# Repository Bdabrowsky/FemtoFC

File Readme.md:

# Hardware files for Open Source flight computer for small diameter rockets
## 17,5x50mm 
## For software, visit [Source Page]([https://github.com/Bdabrowsky/Clockwork_Banana](https://github.com/Bdabrowsky/Clockwork_Banana/tree/Clockwork_Banana_FemtoFC))
## All above hardware is made using funding from [Odkrywcy Diamentów](https://odkrywcydiamentow.com.pl/) grant program

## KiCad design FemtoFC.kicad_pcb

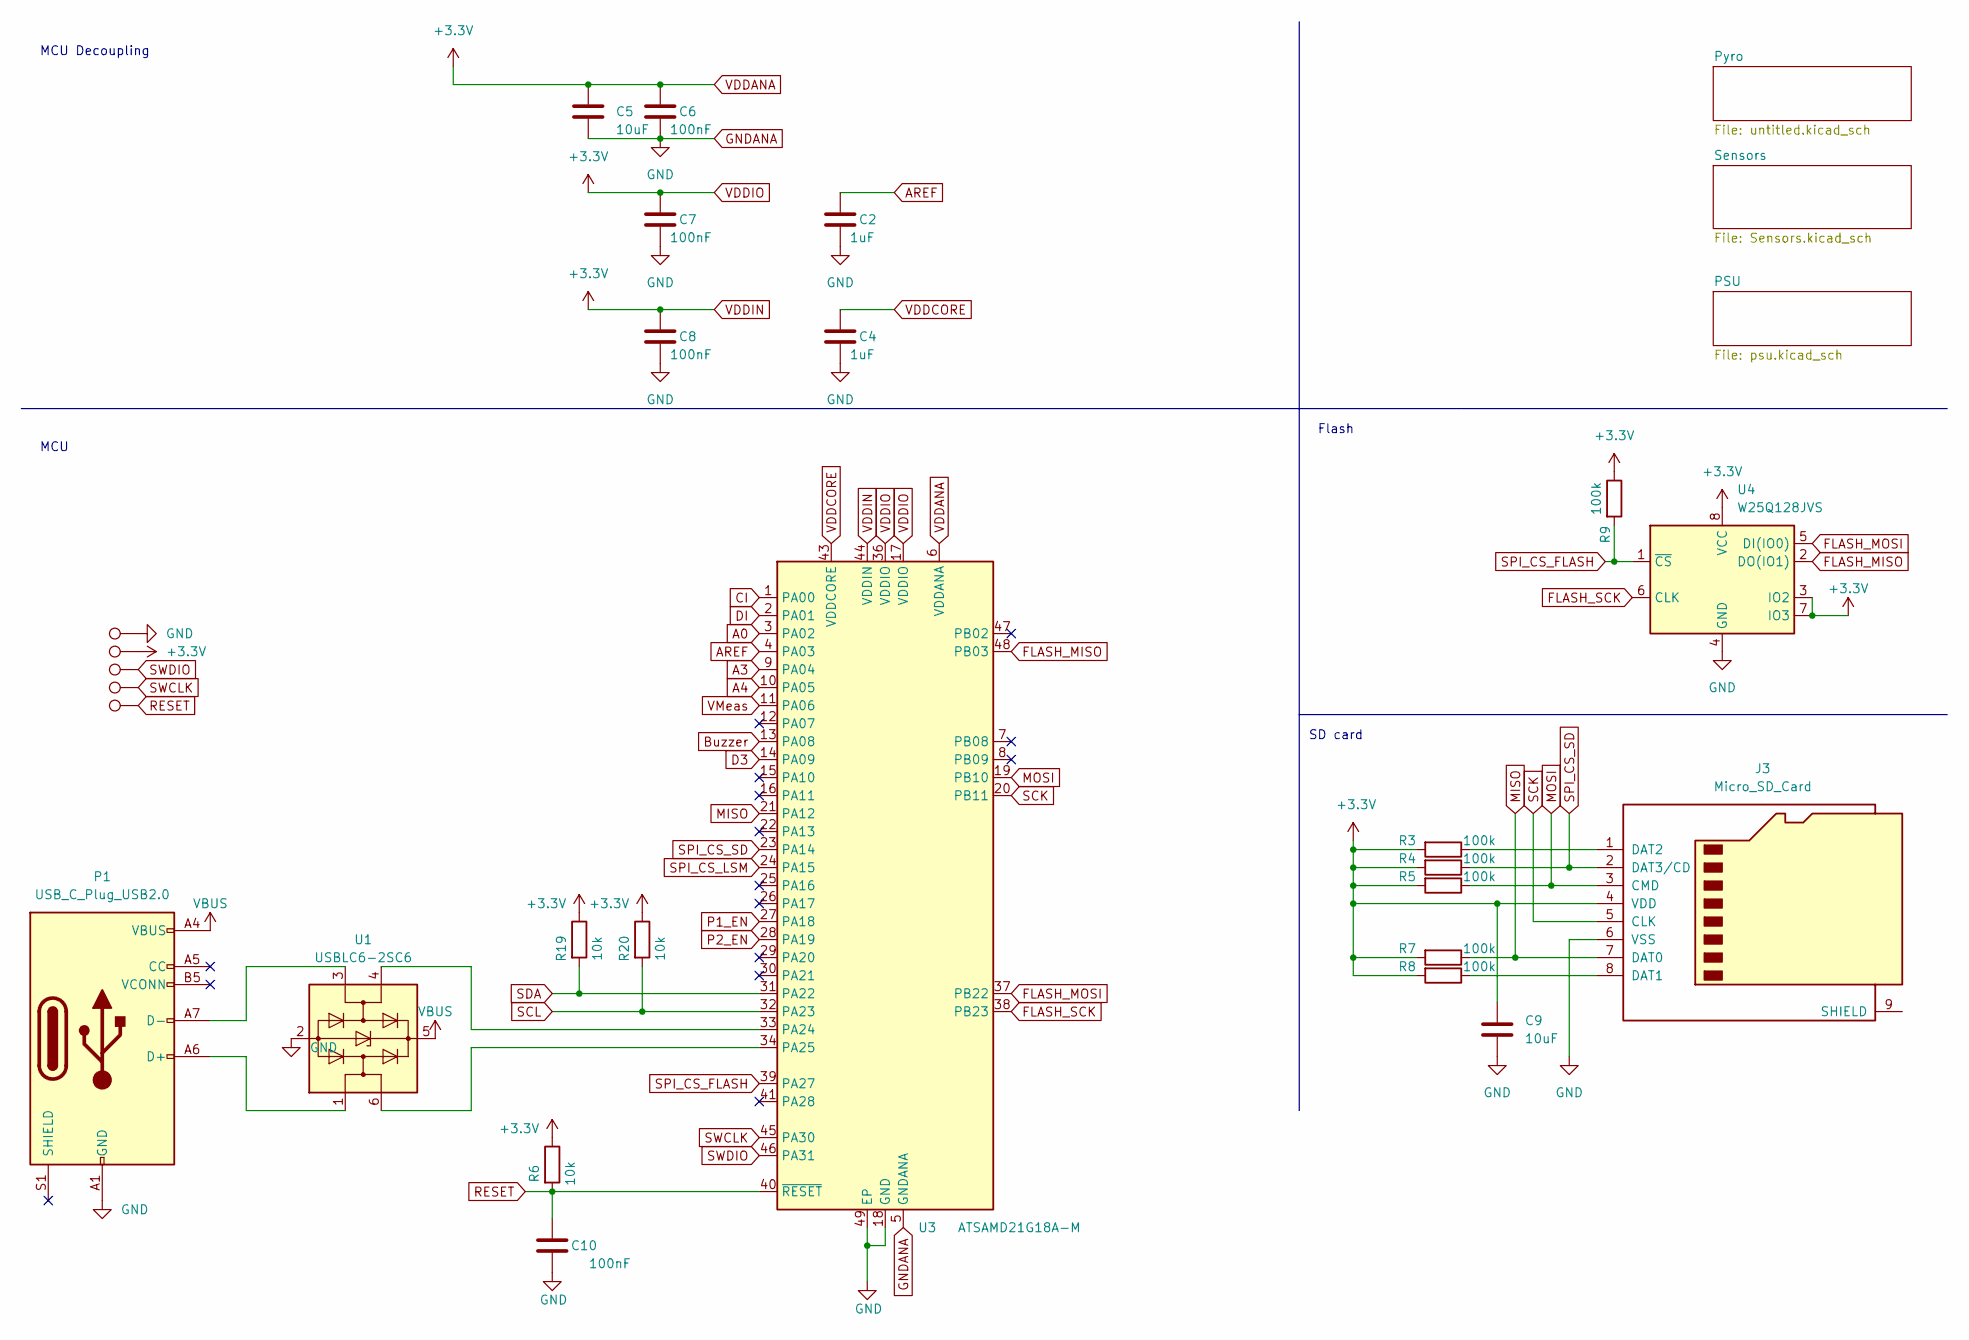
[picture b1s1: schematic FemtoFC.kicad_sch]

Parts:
C2, C4: 1uF; C_0402_1005Metric_Pad0.74x0.62mm_HandSolder
C5, C9: 10uF; C_0402_1005Metric_Pad0.74x0.62mm_HandSolder
C6, C7, C8, C10: 100nF; C_0402_1005Metric_Pad0.74x0.62mm_HandSolder
J3: Micro_SD_Card; microSD_HC_Molex_104031-0811
P1: USB_C_Plug_USB2.0; USB_C_Receptacle_JAE_DX07S016JA1R1500
R3, R4, R5, R7, R8, R9: 100k; R_0402_1005Metric_Pad0.72x0.64mm_HandSolder
R6, R19, R20: 10k; R_0402_1005Metric_Pad0.72x0.64mm_HandSolder
TP1, TP2, TP3, TP4, TP5: TestPoint; TestPoint_Pad_D1.0mm
U1: USBLC6-2SC6; SOT-23-6
U3: ATSAMD21G18A-M; QFN-48-1EP_7x7mm_P0.5mm_EP5.15x5.15mm
U4: W25Q128JVS; WSON-8-1EP_6x5mm_P1.27mm_EP3.4x4.3mm

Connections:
A0: U3.3 (PA02)
A3: U3.9 (PA04)
A4: U3.10 (PA05)
AREF: C2.1, U3.4 (PA03)
Buzzer: U3.13 (PA08); also elsewhere on the board
CI: U3.1 (PA00); also elsewhere on the board
D3: U3.14 (PA09)
DI: U3.2 (PA01); also elsewhere on the board
FLASH_MISO: U3.48 (PB03), U4.2 (DO(IO1))
FLASH_MOSI: U3.37 (PB22), U4.5 (DI(IO0))
FLASH_SCK: U3.38 (PB23), U4.6 (CLK)
GNDANA: C2.2, C4.2, C5.2, C6.2, C7.2, C8.2, C9.2, C10.2, J3.6 (VSS), P1.A1 (GND), P1.A12 (GND), P1.B1 (GND), P1.B12 (GND), TP1.1, U1.2 (GND), U3.5 (GNDANA), U3.18 (GND), U3.35 (GND), U3.42 (GND), U3.49 (EP), U4.4 (GND); also elsewhere on the board
MISO: J3.7 (DAT0), R7.1, U3.21 (PA12); also elsewhere on the board
MOSI: J3.3 (CMD), R5.1, U3.19 (PB10); also elsewhere on the board
unnamed: J3.1 (DAT2), R3.1
unnamed: J3.8 (DAT1), R8.1
unnamed: P1.A6 (D+), U1.1 (I/O1)
unnamed: P1.A7 (D-), U1.3 (I/O2)
unnamed: U1.4 (I/O2), U3.33 (PA24)
unnamed: U1.6 (I/O1), U3.34 (PA25)
P1_EN: U3.27 (PA18); also elsewhere on the board
P2_EN: U3.28 (PA19); also elsewhere on the board
RESET: C10.1, R6.2, TP5.1, U3.40 (~RESET)
SCK: J3.5 (CLK), U3.20 (PB11); also elsewhere on the board
SCL: R20.2, U3.32 (PA23); also elsewhere on the board
SDA: R19.2, U3.31 (PA22); also elsewhere on the board
SPI_CS_FLASH: R9.2, U3.39 (PA27), U4.1 (~CS)
SPI_CS_LSM: U3.24 (PA15); also elsewhere on the board
SPI_CS_SD: J3.2 (DAT3/CD), R4.1, U3.23 (PA14)
SWCLK: TP4.1, U3.45 (PA30)
SWDIO: TP3.1, U3.46 (PA31)
VBUS: P1.A4 (VBUS), P1.A9 (VBUS), P1.B4 (VBUS), P1.B9 (VBUS), U1.5 (VBUS); also elsewhere on the board
VDDANA: C5.1, C6.1, C7.1, C8.1, C9.1, J3.4 (VDD), R3.2, R4.2, R5.2, R6.1, R7.2, R8.2, R9.1, R19.1, R20.1, TP2.1, U3.6 (VDDANA), U3.17 (VDDIO), U3.36 (VDDIO), U3.44 (VDDIN), U4.3 (IO2), U4.7 (IO3), U4.8 (VCC); also elsewhere on the board
VDDCORE: C4.1, U3.43 (VDDCORE)
VMeas: U3.11 (PA06)

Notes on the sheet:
SD card
MCU
Flash
MCU Decoupling

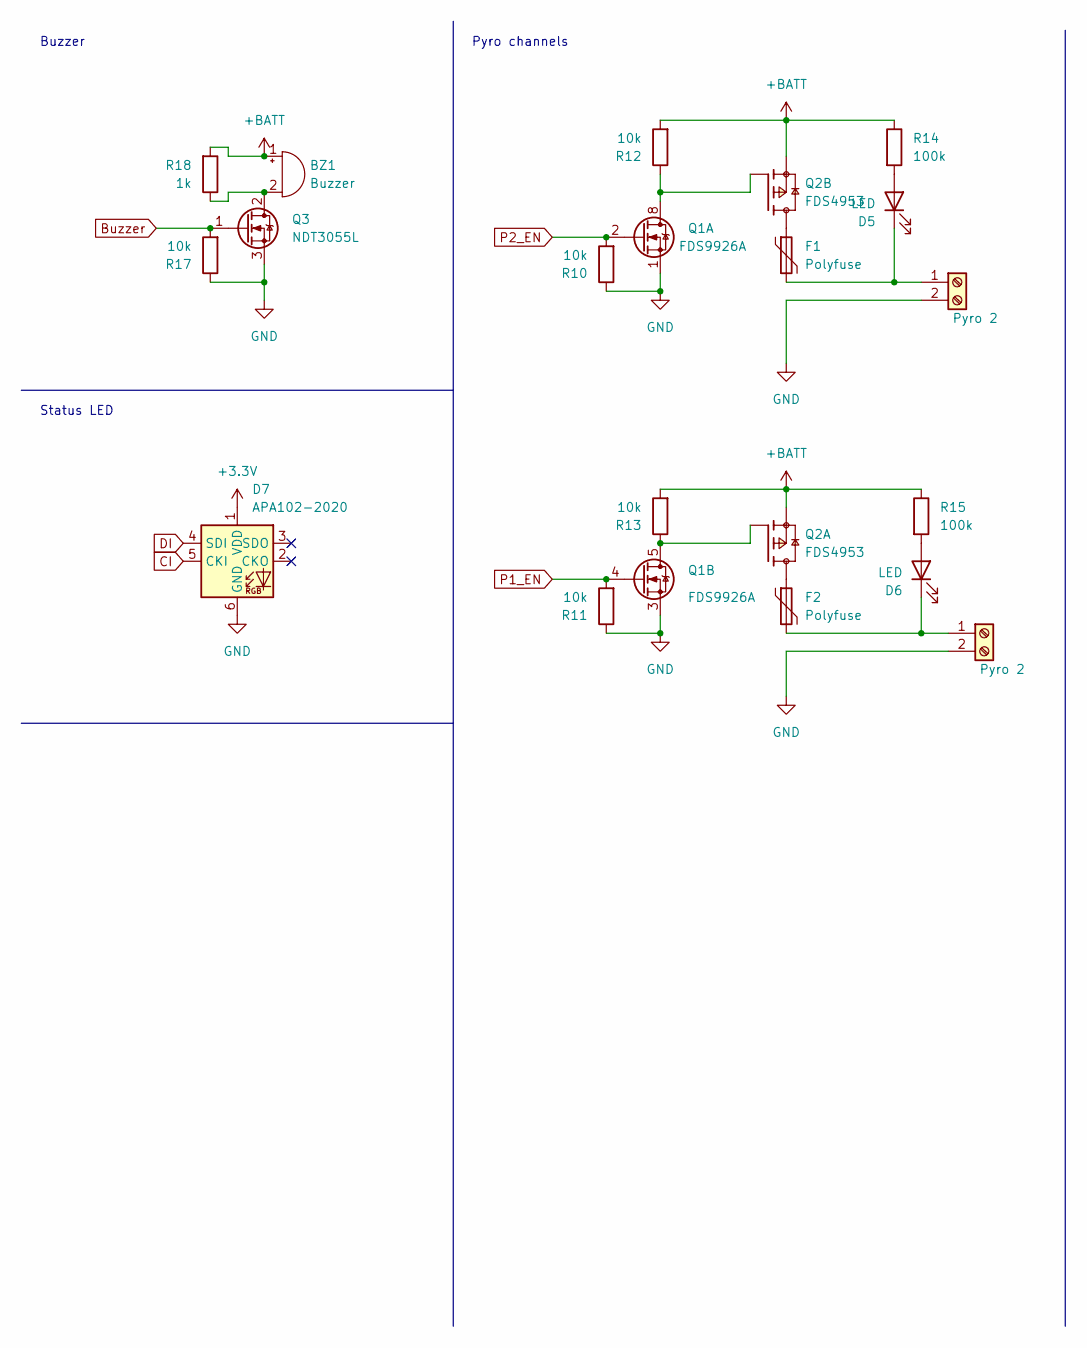
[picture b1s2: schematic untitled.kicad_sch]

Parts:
BZ1: Buzzer; Buzzer_Murata_PKMCS0909E
D5, D6: LED; LED_0603_1608Metric_Pad1.05x0.95mm_HandSolder
D7: APA102-2020; LED-APA102-2020
F1, F2: Polyfuse; Fuse_1206_3216Metric_Pad1.42x1.75mm_HandSolder
J4, J5: Pyro 2; TerminalBlock_Phoenix_MPT-0,5-2-2.54_1x02_P2.54mm_Horizontal
Q1: FDS9926A; SOIC-8_3.9x4.9mm_P1.27mm
Q2: FDS4953; SOIC-8_3.9x4.9mm_P1.27mm
Q3: NDT3055L; TSOT-23
R10, R11, R12, R13, R17: 10k; R_0402_1005Metric_Pad0.72x0.64mm_HandSolder
R14, R15: 100k; R_0402_1005Metric_Pad0.72x0.64mm_HandSolder
R18: 1k; R_0402_1005Metric_Pad0.72x0.64mm_HandSolder

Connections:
+BATT: BZ1.1 (-), Q2.1, Q2.3, R12.2, R13.2, R14.1, R15.1, R18.2; also elsewhere on the board
Buzzer: Q3.1 (G), R17.2; also elsewhere on the board
CI: D7.5 (CKI); also elsewhere on the board
DI: D7.4 (SDI); also elsewhere on the board
GNDANA: D7.6 (GND), J4.2, J5.2, Q1.1 (S1), Q1.3 (S2), Q3.3 (S), R10.1, R11.1, R17.1; also elsewhere on the board
unnamed: BZ1.2 (+), Q3.2 (D), R18.1
unnamed: D5.1 (K), F1.2, J4.1
unnamed: D5.2 (A), R14.2
unnamed: D6.1 (K), F2.2, J5.1
unnamed: D6.2 (A), R15.2
unnamed: F1.1, Q2.7, Q2.8
unnamed: F2.1, Q2.5, Q2.6
unnamed: Q1.5 (D2), Q1.6 (D2), Q2.4, R13.1
unnamed: Q1.7 (D1), Q1.8 (D1), Q2.2, R12.1
P1_EN: Q1.4 (G2), R11.2; also elsewhere on the board
P2_EN: Q1.2 (G1), R10.2; also elsewhere on the board
VDDANA: D7.1 (VDD); also elsewhere on the board

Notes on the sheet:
Buzzer
Status LED
Pyro channels

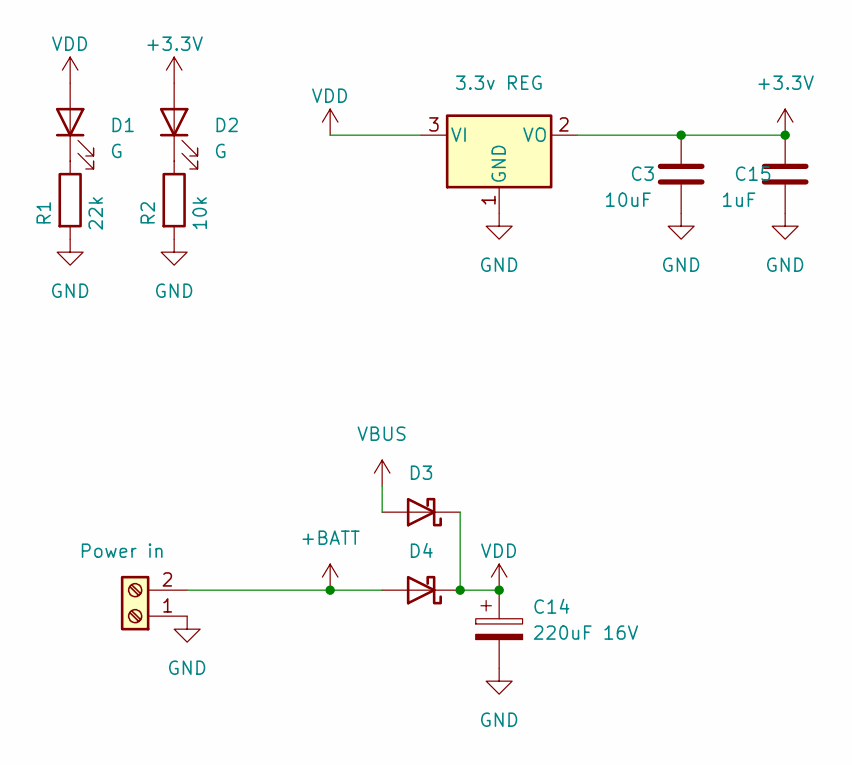
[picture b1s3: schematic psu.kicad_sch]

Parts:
C3: 10uF; C_0402_1005Metric_Pad0.74x0.62mm_HandSolder
C14: 220uF 16V; CP_EIA-7343-31_Kemet-D
C15: 1uF; C_0402_1005Metric_Pad0.74x0.62mm_HandSolder
D1, D2: G; LED_0603_1608Metric
D3, D4: D_Schottky; D_SOD-123
J1: Power in; PinHeader_1x02_P2.54mm_Vertical
R1: 22k; R_0402_1005Metric_Pad0.72x0.64mm_HandSolder
R2: 10k; R_0402_1005Metric_Pad0.72x0.64mm_HandSolder
U2: 3.3v REG; SOT-223-3_TabPin2

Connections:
+BATT: D4.2 (A), J1.2; also elsewhere on the board
GNDANA: C3.2, C14.2, C15.2, J1.1, R1.2, R2.2, U2.1 (GND); also elsewhere on the board
unnamed: D1.1 (K), R1.1
unnamed: D2.1 (K), R2.1
VBUS: D3.2 (A); also elsewhere on the board
VDD: C14.1, D1.2 (A), D3.1 (K), D4.1 (K), U2.3 (VI)
VDDANA: C3.1, C15.1, D2.2 (A), U2.2 (VO); also elsewhere on the board

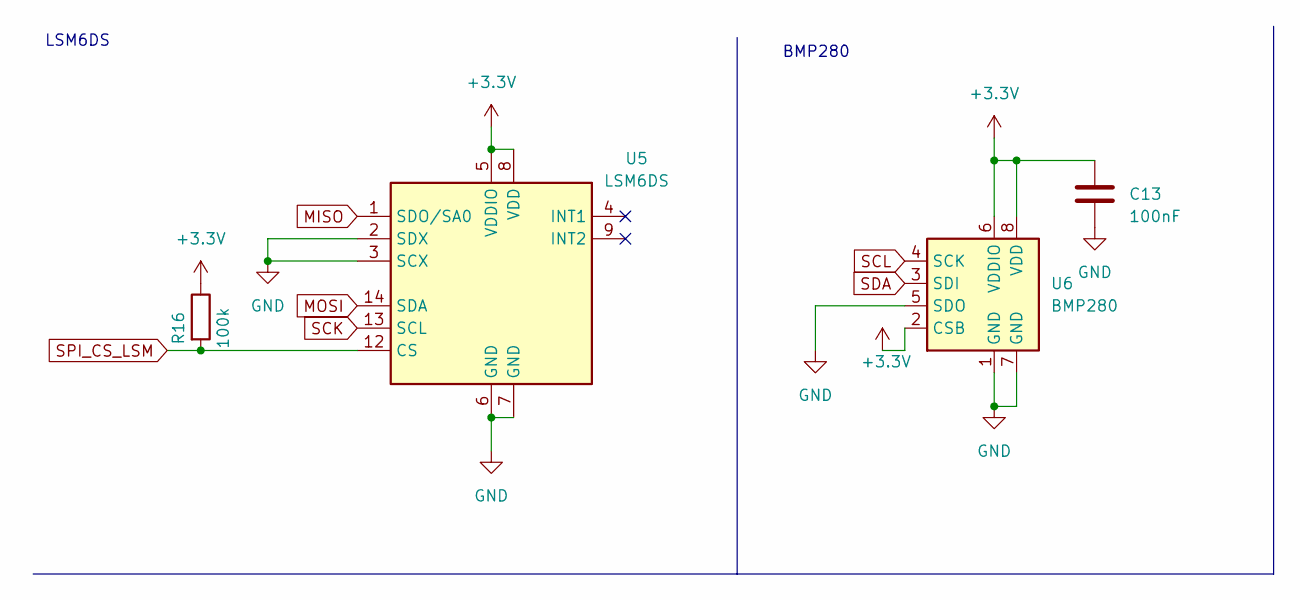
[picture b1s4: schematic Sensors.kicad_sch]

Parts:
C13: 100nF; C_0402_1005Metric_Pad0.74x0.62mm_HandSolder
R16: 100k; R_0402_1005Metric_Pad0.72x0.64mm_HandSolder
U5: LSM6DS; LGA-14_3x2.5mm_P0.5mm_LayoutBorder3x4y
U6: BMP280; Bosch_LGA-8_2x2.5mm_P0.65mm_ClockwisePinNumbering

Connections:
GNDANA: C13.2, U5.2 (SDX), U5.3 (SCX), U5.6 (GND), U5.7 (GND), U6.1 (GND), U6.5 (SDO), U6.7 (GND); also elsewhere on the board
MISO: U5.1 (SDO/SA0); also elsewhere on the board
MOSI: U5.14 (SDA); also elsewhere on the board
SCK: U5.13 (SCL); also elsewhere on the board
SCL: U6.4 (SCK); also elsewhere on the board
SDA: U6.3 (SDI); also elsewhere on the board
SPI_CS_LSM: R16.2, U5.12 (CS); also elsewhere on the board
VDDANA: C13.1, R16.1, U5.5 (VDDIO), U5.8 (VDD), U6.2 (CSB), U6.6 (VDDIO), U6.8 (VDD); also elsewhere on the board

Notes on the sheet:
BMP280
LSM6DS

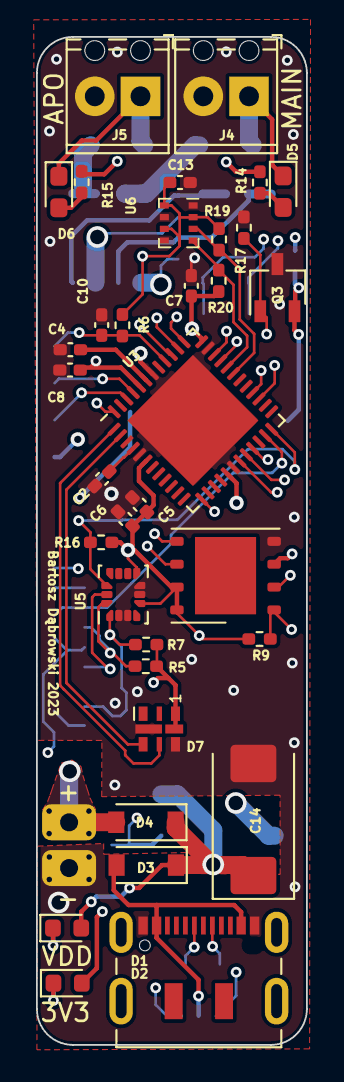
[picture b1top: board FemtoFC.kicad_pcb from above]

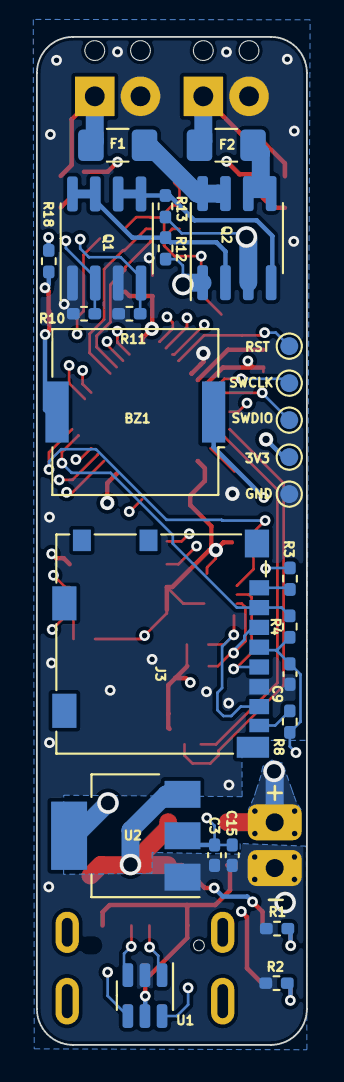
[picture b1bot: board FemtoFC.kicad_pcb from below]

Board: 4 copper layers, 15.0 x 56.0 mm, 61 parts (26 on the bottom side), 43 nets.

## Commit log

2022-09-23 0.2
    PCB edit
    Added 3D models
2022-09-25 Create LICENSE
2023-03-13 Rework for prototype 2
2023-05-27 Rev 27052023
2023-06-18 fixed ground short
2023-12-02 Shortcircuit fix, maybe final version before rev2
2024-02-15 Removed a bunch of DRC warnings
